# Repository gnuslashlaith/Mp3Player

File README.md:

# MP3-Player 

Hello I am Laith and this is my mp3player project. It's a handheld device that can carry 128G worth of music so I can listen to my favorite stuff without using Spotify or something. I had so much fun making the demos and stuff
especially with the journalling. To start, I researched about each of the components that I knew I would need: some form of MP3 module, an OLED display, Pi-Pico, a speaker of some sort, and some buttons. Then, I tinkered
with each of the components indvidually. Im pretty familiar with the pi pico so it wasn't so bad, but I used mostly digital connections (buttons, stepper motors and such), but analog/more complex components, like an entire mp3-module, was quite 
new for me. I had to really think about voltage regulation and keeping the components from frying.

I did fry them once, hehe. But that was because it was like 2 AM and i put all the pins on the wrong side.

Also this is the first time I've avoided using any step-by-step video tutorial. It was entirely based on what I knew from the component research (TX/RX connections, UART, analog vs digital pins !!), which made this project feel all the more
rewarding. I still do not have the physical PCB but I did design it and I have the prototype on a breadboard. heheh. Cool stuff!!

I struggled quite a bit with the code since debugging was quite hard, but it was mostly trial and error. Fun! 

total hours: 15.2 hours

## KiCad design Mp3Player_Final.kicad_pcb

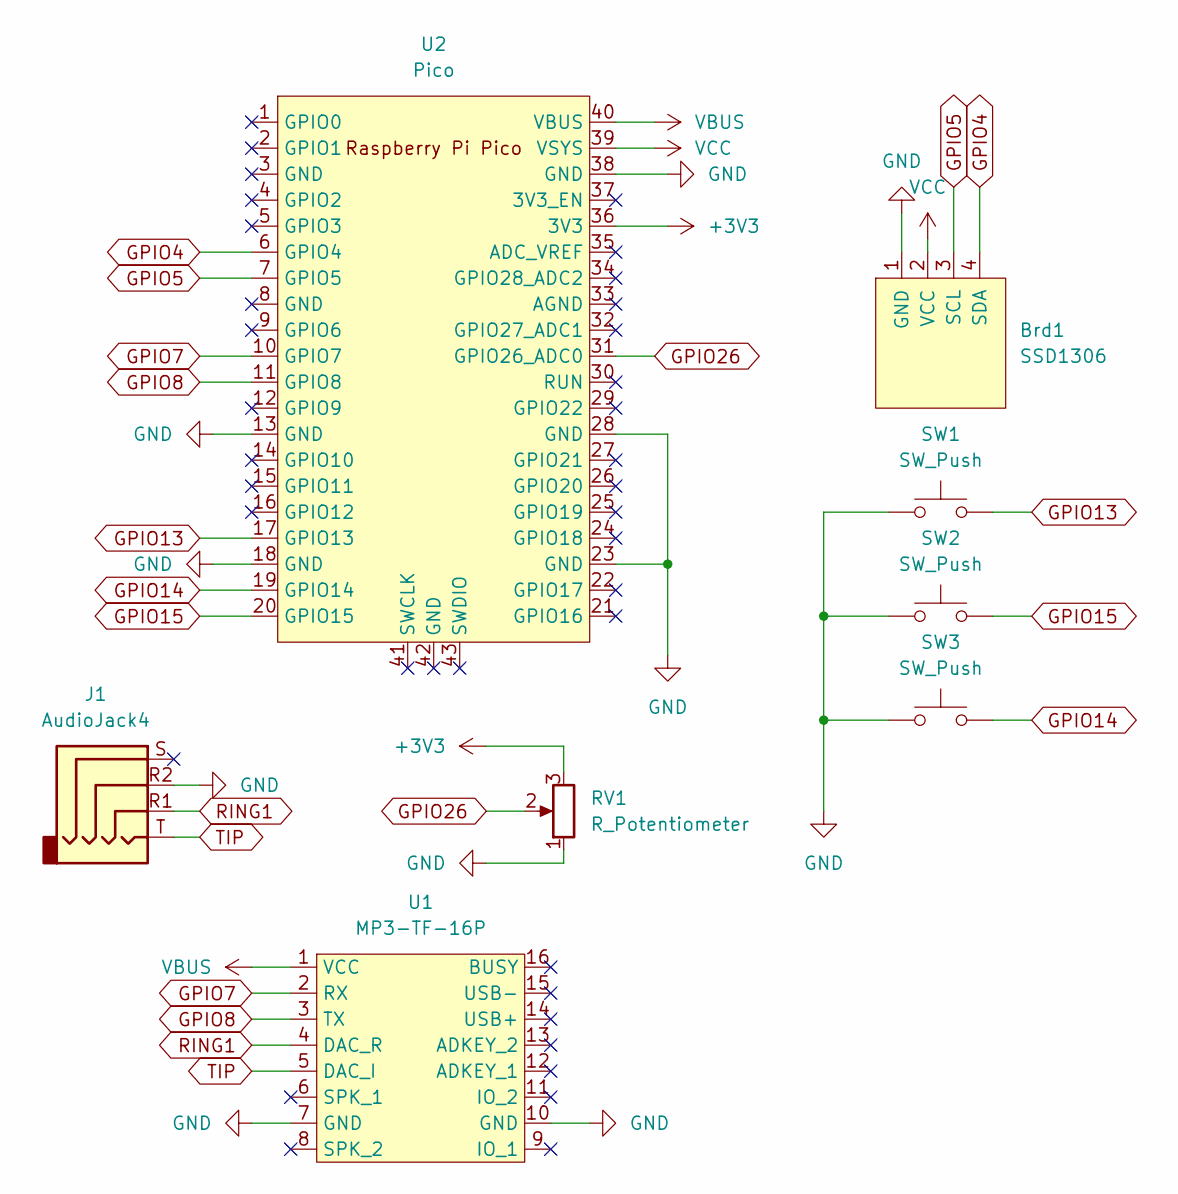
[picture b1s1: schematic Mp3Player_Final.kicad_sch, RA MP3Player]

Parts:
Brd1: SSD1306; 128x64OLED
J1: AudioJack4; TTRS_Breakout_board
RV1: R_Potentiometer; Potentiometer_ACP_CA9-H2,5_Horizontal
SW1, SW2, SW3: SW_Push; SW_PUSH_6mm
U1: MP3-TF-16P; DFPlayer
U2: Pico; RPi_Pico_SMD_TH

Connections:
+3V3: RV1.3, U2.36 (3V3)
GND: Brd1.1 (GND), J1.R2, RV1.1, SW1.1, SW2.1, SW3.1, U1.7 (GND), U1.10 (GND), U2.13 (GND), U2.18 (GND), U2.23 (GND), U2.28 (GND), U2.38 (GND)
GPIO4: Brd1.4 (SDA), U2.6 (GPIO4)
GPIO5: Brd1.3 (SCL), U2.7 (GPIO5)
GPIO7: U1.2 (RX), U2.10 (GPIO7)
GPIO8: U1.3 (TX), U2.11 (GPIO8)
GPIO13: SW1.2, U2.17 (GPIO13)
GPIO14: SW3.2, U2.19 (GPIO14)
GPIO15: SW2.2, U2.20 (GPIO15)
GPIO26: RV1.2, U2.31 (GPIO26_ADC0)
RING1: J1.R1, U1.4 (DAC_R)
TIP: J1.T, U1.5 (DAC_I)
VBUS: U1.1 (VCC), U2.40 (VBUS)
VCC: Brd1.2 (VCC), U2.39 (VSYS)

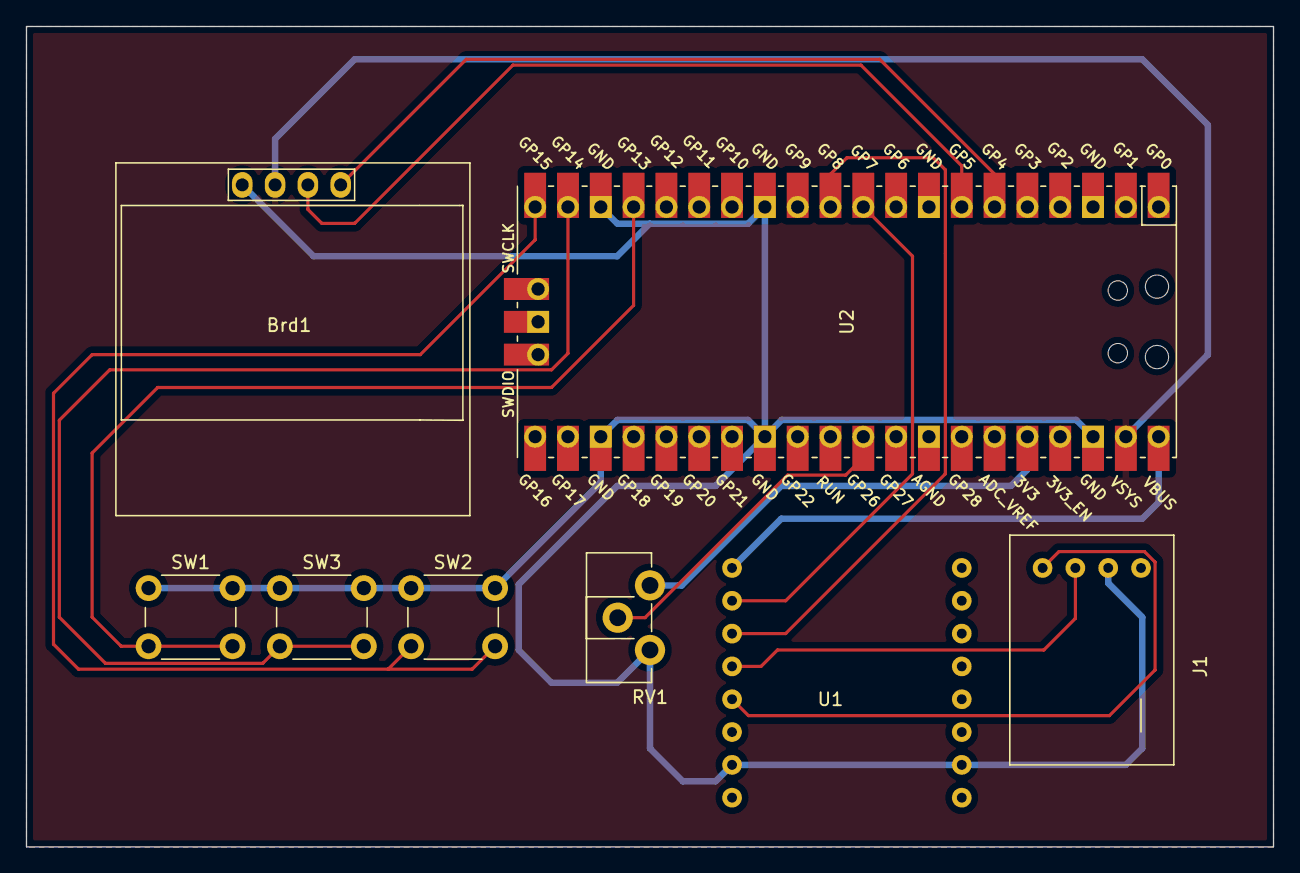
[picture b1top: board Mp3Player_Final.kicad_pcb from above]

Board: 2 copper layers, 96.5 x 63.5 mm, 8 parts (0 on the bottom side), 14 nets.

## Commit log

2025-06-11 Add RAMP3_1
2025-06-11 Update RAMP3_1
2025-06-11 Added Journal and some code
2025-10-17 add files via upload and stuff
2025-10-17 Add README for MP3-Player project
    Added project description and personal insights about the MP3 player development process.
2025-10-17 Update README with images and badge
    Added images and Athena Award badge to README.
2025-10-17 Update README with total hours spent
    Added total hours spent on the project.
